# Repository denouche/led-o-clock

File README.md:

# Led'o'clock

> 🚧 WORK IN PROGRESS: This project is currently under active development. Files and documentation may change frequently.

Led'o'clock is a smart, connected, visual nightlight and time indicator designed to help kids understand when it's time to sleep, play, or wake up. 

This monorepo contains everything you need to build your own: the custom PCB, the 3D printable enclosure, and the ESP32 firmware.

## Usage

### LED Color Code

During normal operation, the ring displays the color defined in the active time slot of your schedule.

> Note that if no schedule is set, the ring will remain off. It's the initial state after configuring WiFi.

The LED ring also provides visual feedback for system events:

| Color | Meaning |
| :--- | :--- |
| 🔵 Light Blue | Device is booting and connecting to WiFi. |
| 🟡 Yellow | WiFi configuration mode — Access Point active. |
| 🟢 Green (×5 blinks) | WiFi connection successful. |
| 🟣 Purple | OTA firmware update in progress. |
| 🔴 Red (×5 blinks) | Factory Reset in progress. |

### Factory Reset

To reset the device to factory settings (wipes WiFi credentials and all configuration):

1. Hold the button on the back of the device for **5 seconds**.
2. The LED ring will start **blinking red** to confirm the reset is in progress.
3. The device restarts in Access Point mode, ready to be reconfigured.

## Features

* **Visual Time Tracking:** Uses a WS2812B LED ring to display specific colors based on the time of day.
* **Progressive Countdown:** LEDs turn off one by one to visually show how much time is left before the next scheduled event.
* **Custom Offline Schedules:** Define daily time slots with personalized hex colors and day-of-week customization. Once the initial time is synced via NTP at boot, the execution is 100% local and will continue to work perfectly even during internet outages.
* **Web Dashboard:** A standalone, mobile-friendly interface to configure the device on your local network.
* **REST API:** Fully controllable via HTTP endpoints for seamless integration with Home Assistant and other automation platforms.
* **OTA Firmware Updates:** Update the firmware over the air without physical access to the device.
* **Easy Setup:** Built-in captive portal for initial WiFi configuration.

## Web interface 

Here is the web dashboard served by the device:

Here is the configuration page, where you can set the colors, time slots, and timezone:

## Getting Started

The project is split into three main directories. Check the `README.md` inside each folder for specific instructions:

1. **`/pcb`**: KiCad schematics files to manufacture the board (designed around the ESP32-C3).
2. **`/enclosure`**: FreeCAD source file and ready-to-print STL files for the case.
3. **`/firmware`**: PlatformIO project containing the C++ source code. 

## License

**CC BY-NC-SA 4.0** (Creative Commons Attribution-NonCommercial-ShareAlike 4.0)

You are free to build, use, and modify this project for **personal use only**. 
You may **not** sell the source code, hardware files, 3D models, or the physical device itself. 
If you remix, adapt, or build upon the material, you must distribute your contributions under the **same license** as the original, credit the original author (Antoine Leveugle), and link back to this repository.

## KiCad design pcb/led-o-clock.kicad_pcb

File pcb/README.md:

# Led'o'clock PCB

> 🚧 WORK IN PROGRESS: The v3.2 PCB design is currently being finalized. Files and documentation may change frequently.
> This v3.2 version will not require any manual soldering, as all components (including the USB-C module) are now designed for SMD assembly by JLCPCB. The documentation below still applies to the previous v3.0 version which requires some manual soldering.

This folder contains the KiCad design files, manufacturing data, and documentation for the Led'o'clock custom board.

The board is built around the **ESP32-C3** microcontroller. To optimize production costs, the surface-mount devices (SMD) are designed to be assembled by JLCPCB, but **some manual soldering is required** to complete the board.

## 1. Manufacturing (JLCPCB PCBA)

The PCB is designed for partial assembly (SMD only) using JLCPCB's "Basic" parts.

1. Go to JLCPCB and upload the Gerber archive: `jlcpcb/production_files/GERBER-led-o-clock.zip`.
2. Enable the **PCB Assembly (PCBA)** option (Top side only).
3. Upload the Bill of Materials: `jlcpcb/production_files/BOM-led-o-clock.csv`.
4. Upload the Pick and Place file: `jlcpcb/production_files/CPL-led-o-clock.csv`.

*Note: Although the through-hole components listed below have footprints and LCSC part numbers in the KiCad project, they were intentionally excluded from the automated assembly files to minimize factory setup fees.*

Here is the resulting board you should receive from the factory, with all SMD components pre-soldered:

## 2. Required Manual Soldering

Once you receive the partially assembled boards from the factory, you must manually solder the following through-hole components:

* **USB-C Module (6-pin):** A standard 6-pin USB-C female breakout board.
  ⚠️ **IMPORTANT:** The module **must** feature two **5.1kΩ pull-down resistors** on the CC1 and CC2 pins. Without these resistors, the device will NOT work with USB-C to USB-C cables or PD chargers.

* **JST PH 2.0 Connector (3-pin):** A horizontal female connector to plug in the LED ring.
* **Capacitor:** A 330µF electrolytic capacitor for power smoothing. *(Pay attention to the polarity!)*
* **Tactile Switch:** A 6x6mm push button. **Important:** This component must be soldered on the **BOTTOM side** of the PCB so it aligns properly with the 3D printed enclosure hole.

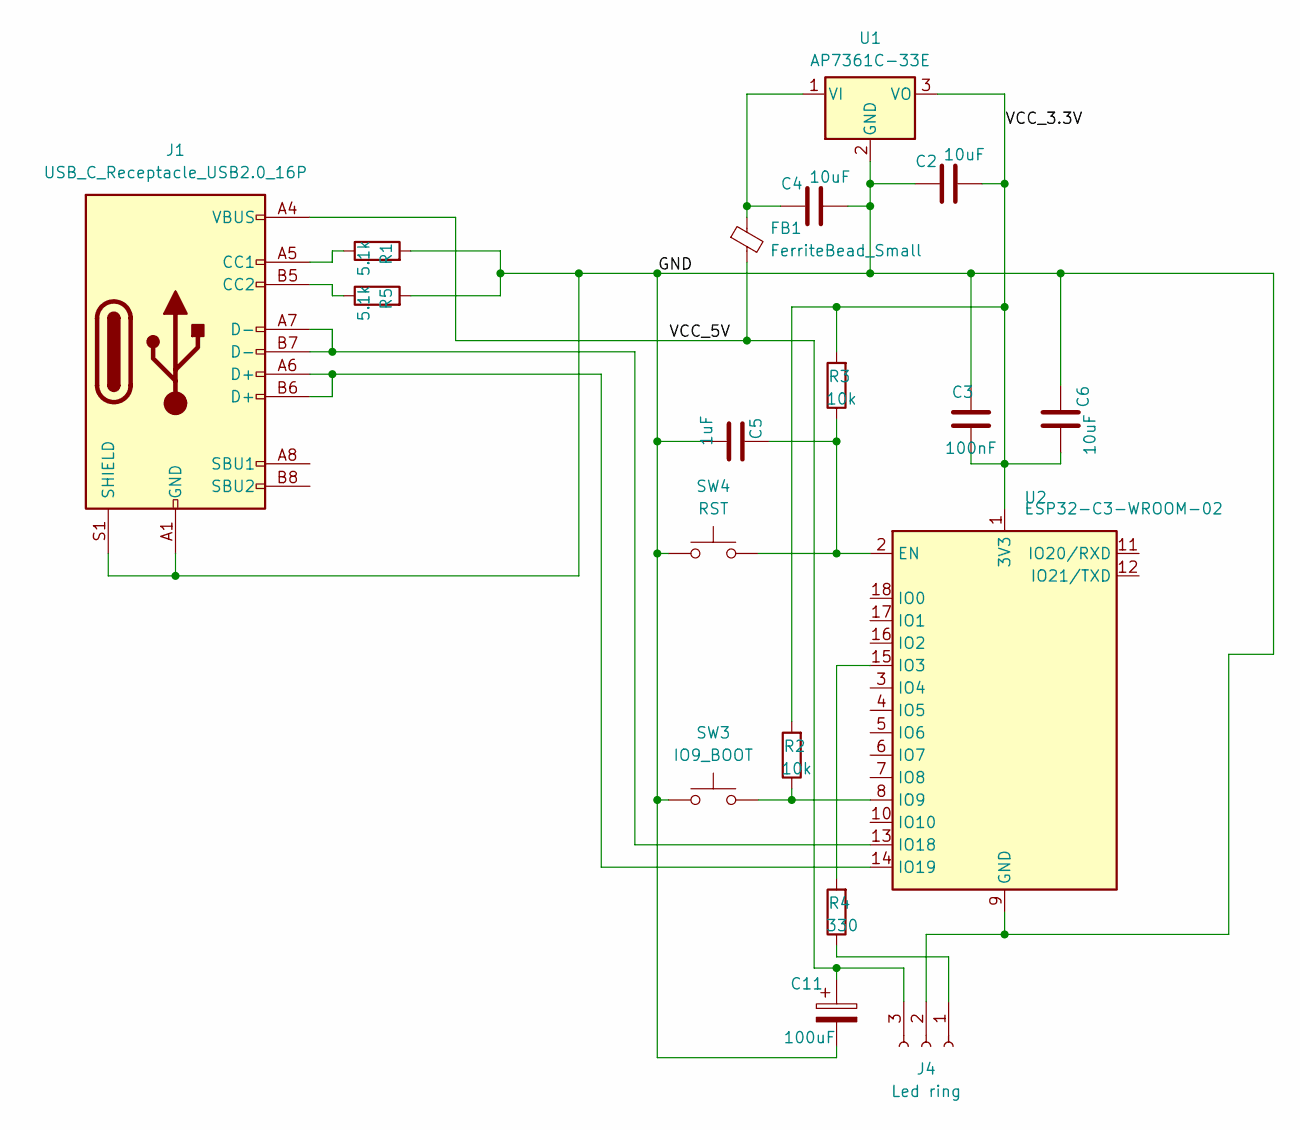
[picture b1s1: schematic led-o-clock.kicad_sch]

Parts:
C2, C4, C6: 10uF; C_1206_3216Metric; LCSC PN C13585
C3: 100nF; C_1206_3216Metric; LCSC PN C24497
C5: 1uF; C_1206_3216Metric; LCSC PN C1848
C11: 100uF; CP_Elec_6.3x5.4; LCSC PN C2887276
FB1: FerriteBead_Small; L_0603_1608Metric; LCSC PN C14709
J1: USB_C_Receptacle_USB2.0_16P; USB_C_Receptacle_HRO_TYPE-C-31-M-12; LCSC PN C165948
J4: Led ring; JST_PH_S3B-PH-K_1x03_P2.00mm_Horizontal; LCSC PN C157929
R1, R5: 5.1k; R_0805_2012Metric; LCSC PN C27834
R2, R3: 10k; R_0805_2012Metric; LCSC PN C17414
R4: 330; R_0805_2012Metric; LCSC PN C17630
SW3: IO9_BOOT; SW_SPST_TS-1088-xR020; LCSC PN C720477
SW4: RST; SW_SPST_TS-1088-xR020; LCSC PN C720477
U1: AP7361C-33E; SOT-223-3_TabPin2; LCSC PN C500795
U2: ESP32-C3-WROOM-02; LCSC PN C2934560

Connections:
/GND: C2.2, C3.1, C4.1, C5.2, C6.2, C11.2, J1.A1 (GND), J1.A12 (GND), J1.B1 (GND), J1.B12 (GND), J1.S1 (SHIELD), J4.2, R1.2, R5.2, SW3.1, SW4.1, U1.2 (GND), U2.9 (GND), U2.19 (GND)
/VCC_3.3V: C2.1, C3.2, C6.1, R2.2, R3.2, U1.3 (VO), U2.1 (3V3)
/VCC_5V: C11.1, FB1.2, J1.A4 (VBUS), J1.A9 (VBUS), J1.B4 (VBUS), J1.B9 (VBUS), J4.3
unnamed: J1.A5 (CC1), R1.1
unnamed: J1.B5 (CC2), R5.1
unnamed: J4.1, R4.1
unnamed: C4.2, FB1.1, U1.1 (VI)
unnamed: C5.1, R3.1, SW4.2, U2.2 (EN)
unnamed: R4.2, U2.15 (IO3)
unnamed: R2.1, SW3.2, U2.8 (IO9)
unnamed: J1.A7 (D-), J1.B7 (D-), U2.13 (IO18)
unnamed: J1.A6 (D+), J1.B6 (D+), U2.14 (IO19)

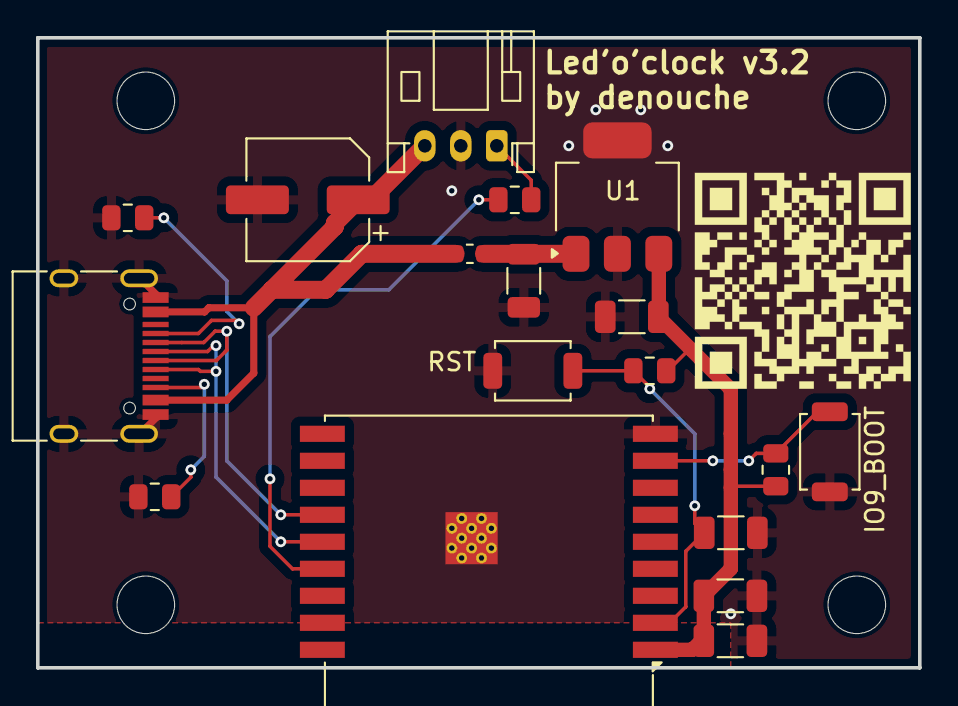
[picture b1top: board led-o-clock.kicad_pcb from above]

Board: 2 copper layers, 49.0 x 35.0 mm, 18 parts (0 on the bottom side), 12 nets.

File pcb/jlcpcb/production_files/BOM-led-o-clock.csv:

Comment,Designator,Footprint,LCSC,Quantity
100nF,C3,C_1206_3216Metric,C24497,1
100uF,C11,CP_Elec_6.3x5.4,C2887276,1
10k,"R2,R3",R_0805_2012Metric,C17414,2
10uF,"C2,C4,C6",C_1206_3216Metric,C13585,3
1uF,C5,C_1206_3216Metric,C1848,1
330,R4,R_0805_2012Metric,C17630,1
5.1k,"R1,R5",R_0805_2012Metric,C27834,2
AP7361C-33E,U1,SOT-223-3_TabPin2,C500795,1
ESP32-C3-WROOM-02,U2,ESP32-C3-WROOM-02,C2934560,1
FerriteBead_Small,FB1,L_0603_1608Metric,C14709,1
IO9_BOOT,SW3,SW_SPST_TS-1088-xR020,C720477,1
Led ring,J4,JST_PH_S3B-PH-K_1x03_P2.00mm_Horizontal,C157929,1
RST,SW4,SW_SPST_TS-1088-xR020,C720477,1
USB_C_Receptacle_USB2.0_16P,J1,USB_C_Receptacle_HRO_TYPE-C-31-M-12,C165948,1

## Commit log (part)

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2026-04-11 feat: add firmware
2026-04-11 feat: add ci workflows
2026-04-11 chore(release): 0.1.0 [skip ci]
    # [0.1.0](https://github.com/denouche/led-o-clock/compare/0.0.1...0.1.0) (2026-04-11)
    ### Features
    * add ci workflows ([776b9b9](https://github.com/denouche/led-o-clock/commit/776b9b9ad46168cb7f1f9bd4b5ebaec1965b2cb0))
2026-04-11 Notes added by 'git notes add'
2026-04-11 fix(firmware): improve success toast when saving configuration
2026-04-11 fix: fix release firmware publish
2026-04-11 chore(release): 0.1.1 [skip ci]
    ## [0.1.1](https://github.com/denouche/led-o-clock/compare/0.1.0...0.1.1) (2026-04-11)
    ### Bug Fixes
    * **firmware:** improve success toast when saving configuration ([ac17b20](https://github.com/denouche/led-o-clock/commit/ac17b20a670e8e572bbc93c68a41e2f8bcd23e4a))
    * fix release firmware publish ([7784a4f](https://github.com/denouche/led-o-clock/commit/7784a4fffaed6dbe78a8b9fdbee2c75096bf966c))
2026-04-11 feat(firmware): add OTA update support
2026-04-11 chore(release): 0.2.0 [skip ci]
    # [0.2.0](https://github.com/denouche/led-o-clock/compare/0.1.1...0.2.0) (2026-04-11)
    ### Features
    * **firmware:** add OTA update support ([87618de](https://github.com/denouche/led-o-clock/commit/87618deee0467314c9d811fd38103e1c16b057e7))
2026-04-11 fix(firmware): add missing firmware upgrade documentation on index
2026-04-11 chore(release): 0.2.1 [skip ci]
    ## [0.2.1](https://github.com/denouche/led-o-clock/compare/0.2.0...0.2.1) (2026-04-11)
    ### Bug Fixes
    * **firmware:** add missing firmware upgrade documentation on index ([eac0821](https://github.com/denouche/led-o-clock/commit/eac082140b3520e5f0013a624b8bb06c9eb9eabd))
2026-04-11 ci: fix firmware build workflow
2026-04-11 docs: update readme
2026-04-11 ci: fix firmware build environment
2026-04-11 feat(enclosure): add enclosure files
2026-04-11 chore(release): 0.3.0 [skip ci]
    # [0.3.0](https://github.com/denouche/led-o-clock/compare/0.2.1...0.3.0) (2026-04-11)
    ### Features
    * **enclosure:** add enclosure files ([ff69254](https://github.com/denouche/led-o-clock/commit/ff6925458fe482433d2bfd948a1ecf59863dcd38))
2026-04-12 fix(firmware): factory reset feedback is now a red blink 5 times
2026-04-12 refactor: factorize reset code
2026-04-12 code style
2026-04-12 fix(firmware): factory reset feedback is now a red blink 5 times (#1)
2026-04-12 chore(release): 0.3.1 [skip ci]
    ## [0.3.1](https://github.com/denouche/led-o-clock/compare/0.3.0...0.3.1) (2026-04-12)
    ### Bug Fixes
    * **firmware:** factory reset feedback is now a red blink 5 times ([#1](https://github.com/denouche/led-o-clock/issues/1)) ([de2a2db](https://github.com/denouche/led-o-clock/commit/de2a2dbc27fe11c148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
2026-04-12 docs: add assembly guide
2026-04-12 feat(firmware): allow to customize brightness for each schedule
2026-04-12 fix contrast
2026-04-12 add etag on index
2026-04-12 feat(firmware): allow to customize brightness for each schedule (#3)
2026-04-12 chore(release): 0.4.0 [skip ci]
    # [0.4.0](https://github.com/denouche/led-o-clock/compare/0.3.1...0.4.0) (2026-04-12)
    ### Features
    * **firmware:** allow to customize brightness for each schedule ([#3](https://github.com/denouche/led-o-clock/issues/3)) ([9e97505](https://github.com/denouche/led-o-clock/commit/9e97505a7ca961106156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
2026-04-12 feat: change firmware upgrade endpoint from GET to POST with toast feedback
    Agent-Logs-Url: https://github.com/denouche/led-o-clock/sessions/dbed8f9b-f8f0-457f-833e-82375ecef557
2026-04-12 refactor: move showMessage to common.js to deduplicate
    Agent-Logs-Url: https://github.com/denouche/led-o-clock/sessions/ad9293c8-1206-460a-8a2c-8f63a70e0739
2026-04-12 feat: change firmware upgrade endpoint from GET to POST with toast feedback (#4)
2026-04-12 chore(release): 0.5.0 [skip ci]
    # [0.5.0](https://github.com/denouche/led-o-clock/compare/0.4.0...0.5.0) (2026-04-12)
    ### Features
    * change firmware upgrade endpoint from GET to POST with toast feedback ([#4](https://github.com/denouche/led-o-clock/issues/4)) ([71c531c](https://github.com/denouche/led-o-clock/commit/71c531c76bc8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
2026-04-12 feat: show current and latest firmware version on web UI
    - Refactor ota_service to expose FirmwareInfo struct with version + URL
    - Add GET /firmware_check endpoint returning current/latest version JSON
    - Update index.html with firmware info area and conditional update button
    - Update index.js to check firmware version on page load
    Agent-Logs-Url: https://github.com/denouche/led-o-clock/sessions/7e86a7a9-4e3d-4f5d-81ed-9f482081aba4
2026-04-12 fix: use DOM construction instead of innerHTML for firmware version display
    Agent-Logs-Url: https://github.com/denouche/led-o-clock/sessions/7e86a7a9-4e3d-4f5d-81ed-9f482081aba4
2026-04-12 improve firmware list
2026-04-12 feat(firmware): display current and available firmware versions on web UI (#5)
2026-04-12 chore(release): 0.6.0 [skip ci]
    # [0.6.0](https://github.com/denouche/led-o-clock/compare/0.5.0...0.6.0) (2026-04-12)
    ### Features
    * **firmware:** display current and available firmware versions on web UI ([#5](https://github.com/denouche/led-o-clock/issues/5)) ([de0d7cf](https://github.com/denouche/led-o-clock/commit/de0d7cf7bd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
2026-04-29 feat: add pcb folder and work on readme
2026-04-29 chore(release): 0.7.0 [skip ci]
    # [0.7.0](https://github.com/denouche/led-o-clock/compare/0.6.0...0.7.0) (2026-04-29)
    ### Features
    * add pcb folder and work on readme ([51abcd6](https://github.com/denouche/led-o-clock/commit/51abcd60a1240a7f589b55eeadc327e77937034b))
2026-04-29 docs: work on enclosure readme
2026-04-29 fix: separate releases per module
2026-04-29 fix(firmware): fix documentation
2026-04-29 chore(release): 1.0.0 [skip ci]
    # 1.0.0 (2026-04-29)
    ### Bug Fixes
    * **firmware:** add missing firmware upgrade documentation on index ([eac0821](https://github.com/denouche/led-o-clock/commit/eac082140b3520e5f0013a624b8bb06c9eb9eabd))
    * **firmware:** factory reset feedback is now a red blink 5 times ([#1](https://github.com/denouche/led-o-clock/issues/1)) ([de2a2db](https://github.com/denouche/led-o-clock/commit/de2a2dbc27fe11c148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
    * **firmware:** fix documentation ([69edb70](https://github.com/denouche/led-o-clock/commit/69edb7068c953dc65c9f04d9776cdc7684711e32))
    * **firmware:** improve success toast when saving configuration ([ac17b20](https://github.com/denouche/
2026-04-29 ci: fix workflows names
2026-04-29 fix(pcb): move jst connector on the top
2026-04-29 fix(pcb): move jst connector on the top (#6)
2026-04-29 feat(firmware): use gh pages manifest for OTA update
2026-04-29 feat(firmware): use gh pages manifest for OTA update (#7)
2026-04-29 chore(release): 1.1.0 [skip ci]
    # [1.1.0](https://github.com/denouche/led-o-clock/compare/firmware-1.0.0...firmware-1.1.0) (2026-04-29)
    ### Bug Fixes
    * **pcb:** move jst connector on the top ([#6](https://github.com/denouche/led-o-clock/issues/6)) ([a4a3ec3](https://github.com/denouche/led-o-clock/commit/a4a3ec3f5f545fc882d85de9f8cf33023da9cf9b))
    ### Features
    * **firmware:** use gh pages manifest for OTA update ([#7](https://github.com/denouche/led-o-clock/issues/7)) ([9efd22f](https://github.com/denouche/led-o-clock/commit/9efd22f0976dd2a50e7f2274a3ea8f6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
2026-05-07 fix(pcb): improve button placement and add QR code
2026-05-07 docs: add usage section in main readme
2026-05-07 docs: improve readme usage configuration
2026-05-19 feat(pcb): work on v3.2
2026-05-19 feat(enclosure): work on v3.1 enclosure
2026-05-19 docs(pcb): add work in progress v3.2 info
2026-05-21 fix after review
2026-05-21 feat(firmware): add GET /set_leds_on endpoint (#8)
2026-05-21 chore(release): 1.2.0 [skip ci]
    # [1.2.0](https://github.com/denouche/led-o-clock/compare/firmware-1.1.0...firmware-1.2.0) (2026-05-21)
    ### Bug Fixes
    * **pcb:** improve button placement and add QR code ([9fd4abb](https://github.com/denouche/led-o-clock/commit/9fd4abb37743e466d26927f49193d1b6cf61663b))
    ### Features
    * **enclosure:** work on v3.1 enclosure ([44e2d0d](https://github.com/denouche/led-o-clock/commit/44e2d0d0b37f5188ccae702cb5005594614ab368))
    * **firmware:** add GET /set_leds_on endpoint ([#8](https://github.com/denouche/led-o-clock/issues/8)) ([9e0ffce](https://github.com/denouche/led-o-clock/commit/9e0ffcedce582659c4645045b0127e3a8afb4a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
